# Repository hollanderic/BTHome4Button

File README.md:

# BTButton — Ultra-Low-Power 4-Button BTHome v2 BLE Device

Firmware for a CR2032-powered 4-button BLE remote implementing the **BTHome v2** specification, supporting the **PCA10040 (nRF52-DK / nRF52832)**, a **custom nRF52832 PCB**, and the **PicoMicro nRF52840**.

## Features

- **4 Independent Buttons**: Simultaneous, non-blocking per-button state machines (`ButtonStateMachine`) supporting:
  - **Single Press** (`0x01`)
  - **Double Press** (`0x02`)
  - **Long Press** (`0x04`, triggers at 700 ms hold)
  - 25 ms hardware-timer debounce, plus `NRF_P0->LATCH` wake-up seeding (`on_system_off_wake()`) so quick short presses released during bootloader startup are still captured.
- **Single Status LED**: Brief visual feedback during BLE transmission bursts (and a 150 ms pulse when entering the bootloader on PicoMicro).
- **BTHome v2 Advertising (`0xFCD2`)**:
  - Trigger-based device flag (`0x44`, v2 unencrypted)
  - Persistent 8-bit `Packet ID` (`0x00`) retained across System OFF resets (`GPREGRET` on nRF52832, `GPREGRET2` on nRF52840) for receiver deduplication
  - CR2032 `Battery %` (`0x01`) measured via `NRF_SAADC` on internal `VDD`
  - 4x `Button` objects (`0x3A`) in order
  - Complete Local Name (`BTButton`)
- **Ultra-Low-Power Architecture**:
  - **System OFF (`~0.3 µA`)**: MCU sleeps in `SYSTEMOFF` whenever all 4 buttons are idle, waking on any button press via GPIO `SENSE`.
  - **System ON (`~1.9 µA`)**: During active press/debounce/double-press windows, the CPU sleeps in `__WFE()` using `RTC2` (1024 Hz) and `GPIOTE PORT` events via `SEVONPEND` (no polling).
  - **Direct `NRF_RADIO` BLE**: Transmits `ADV_NONCONN_IND` bursts (`10` rounds × `27 ms`, ~243 ms span) on channels 37, 38, and 39 without SoftDevice overhead; HFXO and `RADIO` are powered on only during each TX burst.
  - **USB Disabled at Runtime**: On nRF52840, `NRF_USBD` and `USBD_IRQn` are disabled at startup so TinyUSB cannot preempt BLE bursts or draw extra current.
  - **DC/DC Converter**: Enabled when `BOARD_HAS_DCDC` is `1`.

## Target Differences

| Feature | `pca10040` (default) | `custom_pcb` | `picomicro_nrf52840` |
| :--- | :--- | :--- | :--- |
| **MCU** | nRF52832 | nRF52832 | nRF52840 |
| **Arduino Core** | `arduinonordicnrf5` | `arduinonordicnrf5` | `arduinoadafruitnrf52` |
| **Buttons 1–4** | `P0.13`, `P0.14`, `P0.15`, `P0.16` | Configurable in `board_config.h` | `P0.17`, `P0.20`, `P0.22`, `P0.24` |
| **Button Polarity** | Active-low (pull-up) | Configurable (`BTN_ACTIVE_LOW`) | Active-high (pull-down) |
| **Status LED** | `P0.17` (LED1), active-low | Configurable in `board_config.h` | `P0.15`, active-high |
| **TX Power** | `0 dBm` (`0x00UL`) | `0 dBm` (`0x00UL`) | `+8 dBm` (`0x08UL`, max) |
| **32.768 kHz XTAL** | `BOARD_HAS_LFXTAL = 1` | `BOARD_HAS_LFXTAL = 0` (LFRC) | `BOARD_HAS_LFXTAL = 1` |
| **Packet ID Reg** | `NRF_POWER->GPREGRET` | `NRF_POWER->GPREGRET` | `NRF_POWER->GPREGRET2` |
| **Upload Method** | J-Link (`upload_protocol = jlink`) | J-Link (`upload_protocol = jlink`) | USB DFU (`upload_protocol = nrfutil`) |
| **Bootloader Entry** | N/A | N/A | Hold **Buttons 1 + 4 for 3s** (or double-tap `RST`) |

## Custom PCB Configuration (`env:custom_pcb`)

Edit the `#if defined(BOARD_CUSTOM_PCB)` section in [include/board_config.h](include/board_config.h) to set your custom PCB's GPIO pins, active polarity, `BOARD_HAS_DCDC` (`1` if L2/L3 inductors are populated), and `BOARD_HAS_LFXTAL` (`1` if a 32.768 kHz crystal is populated, `0` to use internal LFRC).

## Build, Flash, and Test

```bash
# Build for PCA10040 (nRF52-DK)
pio run -e pca10040

# Flash to PCA10040 via onboard J-Link
pio run -e pca10040 -t upload

# Build and flash to PicoMicro nRF52840 via USB
# (If already running BTButton firmware, hold Buttons 1 + 4 for 3s or double-tap RST first to enter DFU mode)
pio run -e picomicro_nrf52840 -t upload

# Build for custom PCB
pio run -e custom_pcb

# Run native host unit tests (BTHome packet builder + button state machine)
clang++ -std=c++17 -Wall -Wextra -Iinclude test/test_native/test_main.cpp -o /tmp/btbutton_test && /tmp/btbutton_test
```

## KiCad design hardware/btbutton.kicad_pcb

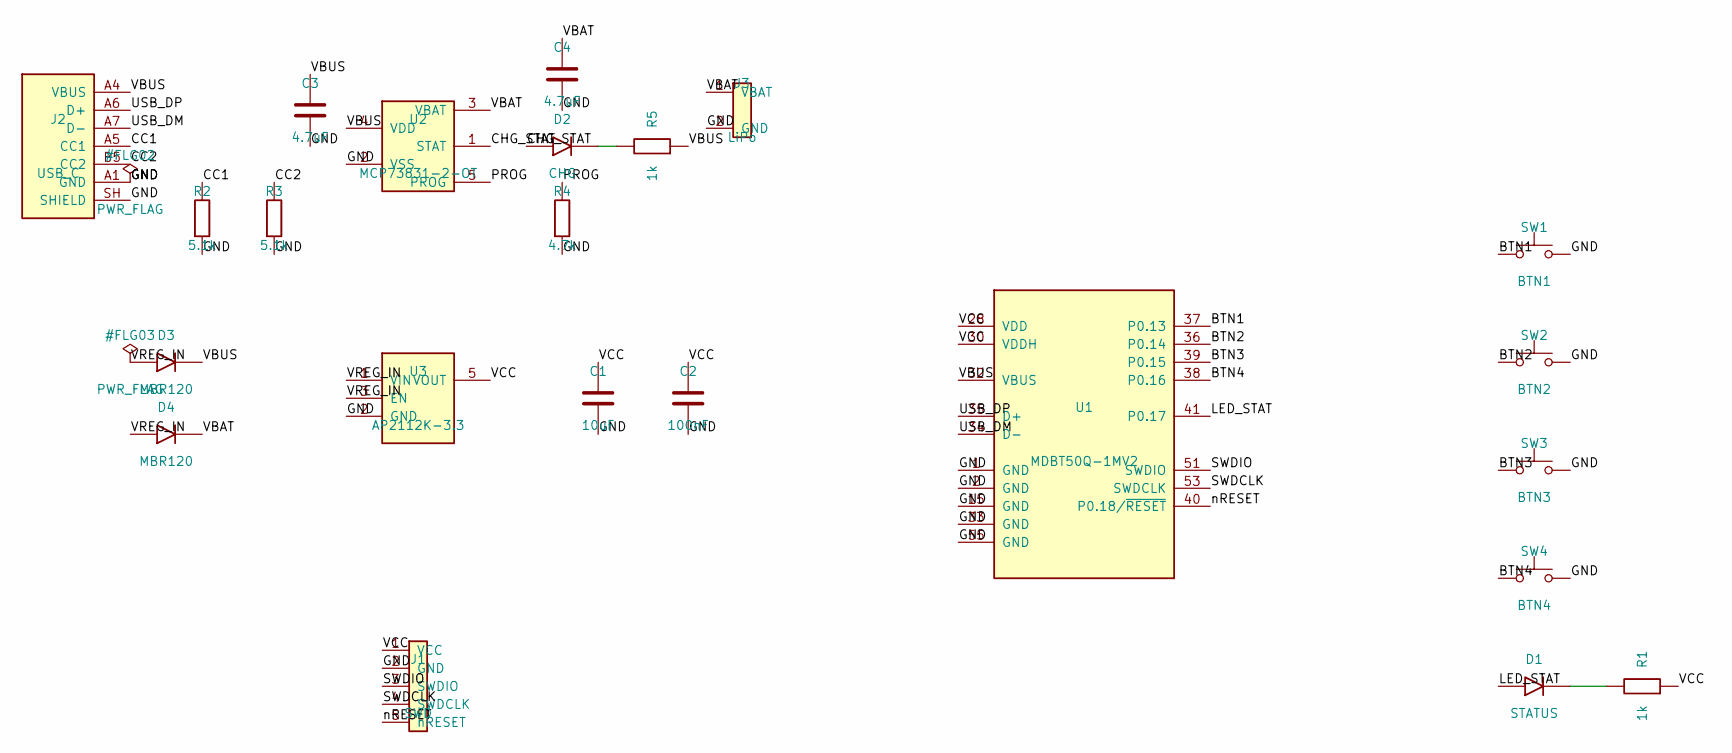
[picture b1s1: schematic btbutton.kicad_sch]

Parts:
C1: 10uF; C_0805_2012Metric
C2: 100nF; C_0603_1608Metric
C3, C4: 4.7uF; C_0603_1608Metric
D1: STATUS; LED_0603_1608Metric
D2: CHG; LED_0603_1608Metric
D3, D4: MBR120; D_SOD-123
J1: SWD; PinHeader_1x05_P2.54mm_Vertical
J2: USB_C; USB_C_Receptacle_GCT_USB4105-xx-A_16P_TopMnt_Horizontal
J3: LiPo; JST_PH_B2B-PH-K_1x02_P2.00mm_Vertical
R1, R5: 1k; R_0603_1608Metric
R2, R3: 5.1k; R_0603_1608Metric
R4: 4.7k; R_0603_1608Metric
SW1: BTN1; SW_SPST_PTS645Sx43SMTR92
SW2: BTN2; SW_SPST_PTS645Sx43SMTR92
SW3: BTN3; SW_SPST_PTS645Sx43SMTR92
SW4: BTN4; SW_SPST_PTS645Sx43SMTR92
U1: MDBT50Q-1MV2; Raytac_MDBT50Q
U2: MCP73831-2-OT; SOT-23-5
U3: AP2112K-3.3; SOT-23-5

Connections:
BTN1: SW1.1, U1.37 (P0.13)
BTN2: SW2.1, U1.36 (P0.14)
BTN3: SW3.1, U1.39 (P0.15)
BTN4: SW4.1, U1.38 (P0.16)
CC1: J2.A5 (CC1), R2.1
CC2: J2.B5 (CC2), R3.1
CHG_A: D2.2 (A), R5.1
CHG_STAT: D2.1 (K), U2.1 (STAT)
GND: C1.2, C2.2, C3.2, C4.2, J1.2 (GND), J2.A1 (GND), J2.A12, J2.B1, J2.B12, J2.SH (SHIELD), J3.2 (GND), R2.2, R3.2, R4.2, SW1.2, SW2.2, SW3.2, SW4.2, U1.1 (GND), U1.2 (GND), U1.15 (GND), U1.33 (GND), U1.55 (GND), U2.2 (VSS), U3.2 (GND)
LED_A: D1.2 (A), R1.1
LED_STAT: D1.1 (K), U1.41 (P0.17)
PROG: R4.1, U2.5 (PROG)
SWDCLK: J1.4 (SWDCLK), U1.53 (SWDCLK)
SWDIO: J1.3 (SWDIO), U1.51 (SWDIO)
USB_DM: J2.A7 (D-), J2.B7, U1.34 (D-)
USB_DP: J2.A6 (D+), J2.B6, U1.35 (D+)
VBAT: C4.1, D4.2 (A), J3.1 (VBAT), U2.3 (VBAT)
VBUS: C3.1, D3.2 (A), J2.A4 (VBUS), J2.A9, J2.B4, J2.B9, R5.2, U1.32 (VBUS), U2.4 (VDD)
VCC: C1.1, C2.1, J1.1 (VCC), R1.2, U1.28 (VDD), U1.30 (VDDH), U3.5 (VOUT)
VREG_IN: D3.1 (K), D4.1 (K), U3.1 (VIN), U3.3 (EN)
nRESET: J1.5 (nRESET), U1.40 (P0.18/~RESET)

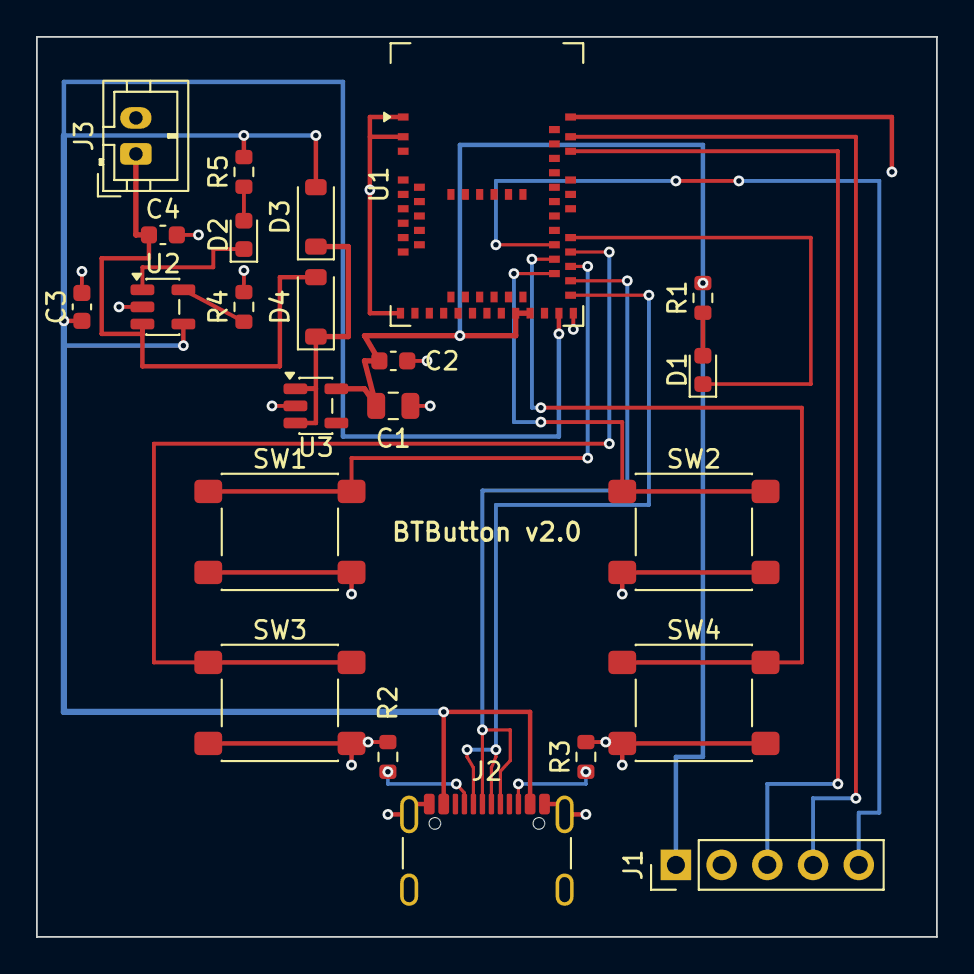
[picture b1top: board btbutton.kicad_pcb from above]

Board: 2 copper layers, 50.0 x 50.0 mm, 23 parts (0 on the bottom side), 21 nets.
